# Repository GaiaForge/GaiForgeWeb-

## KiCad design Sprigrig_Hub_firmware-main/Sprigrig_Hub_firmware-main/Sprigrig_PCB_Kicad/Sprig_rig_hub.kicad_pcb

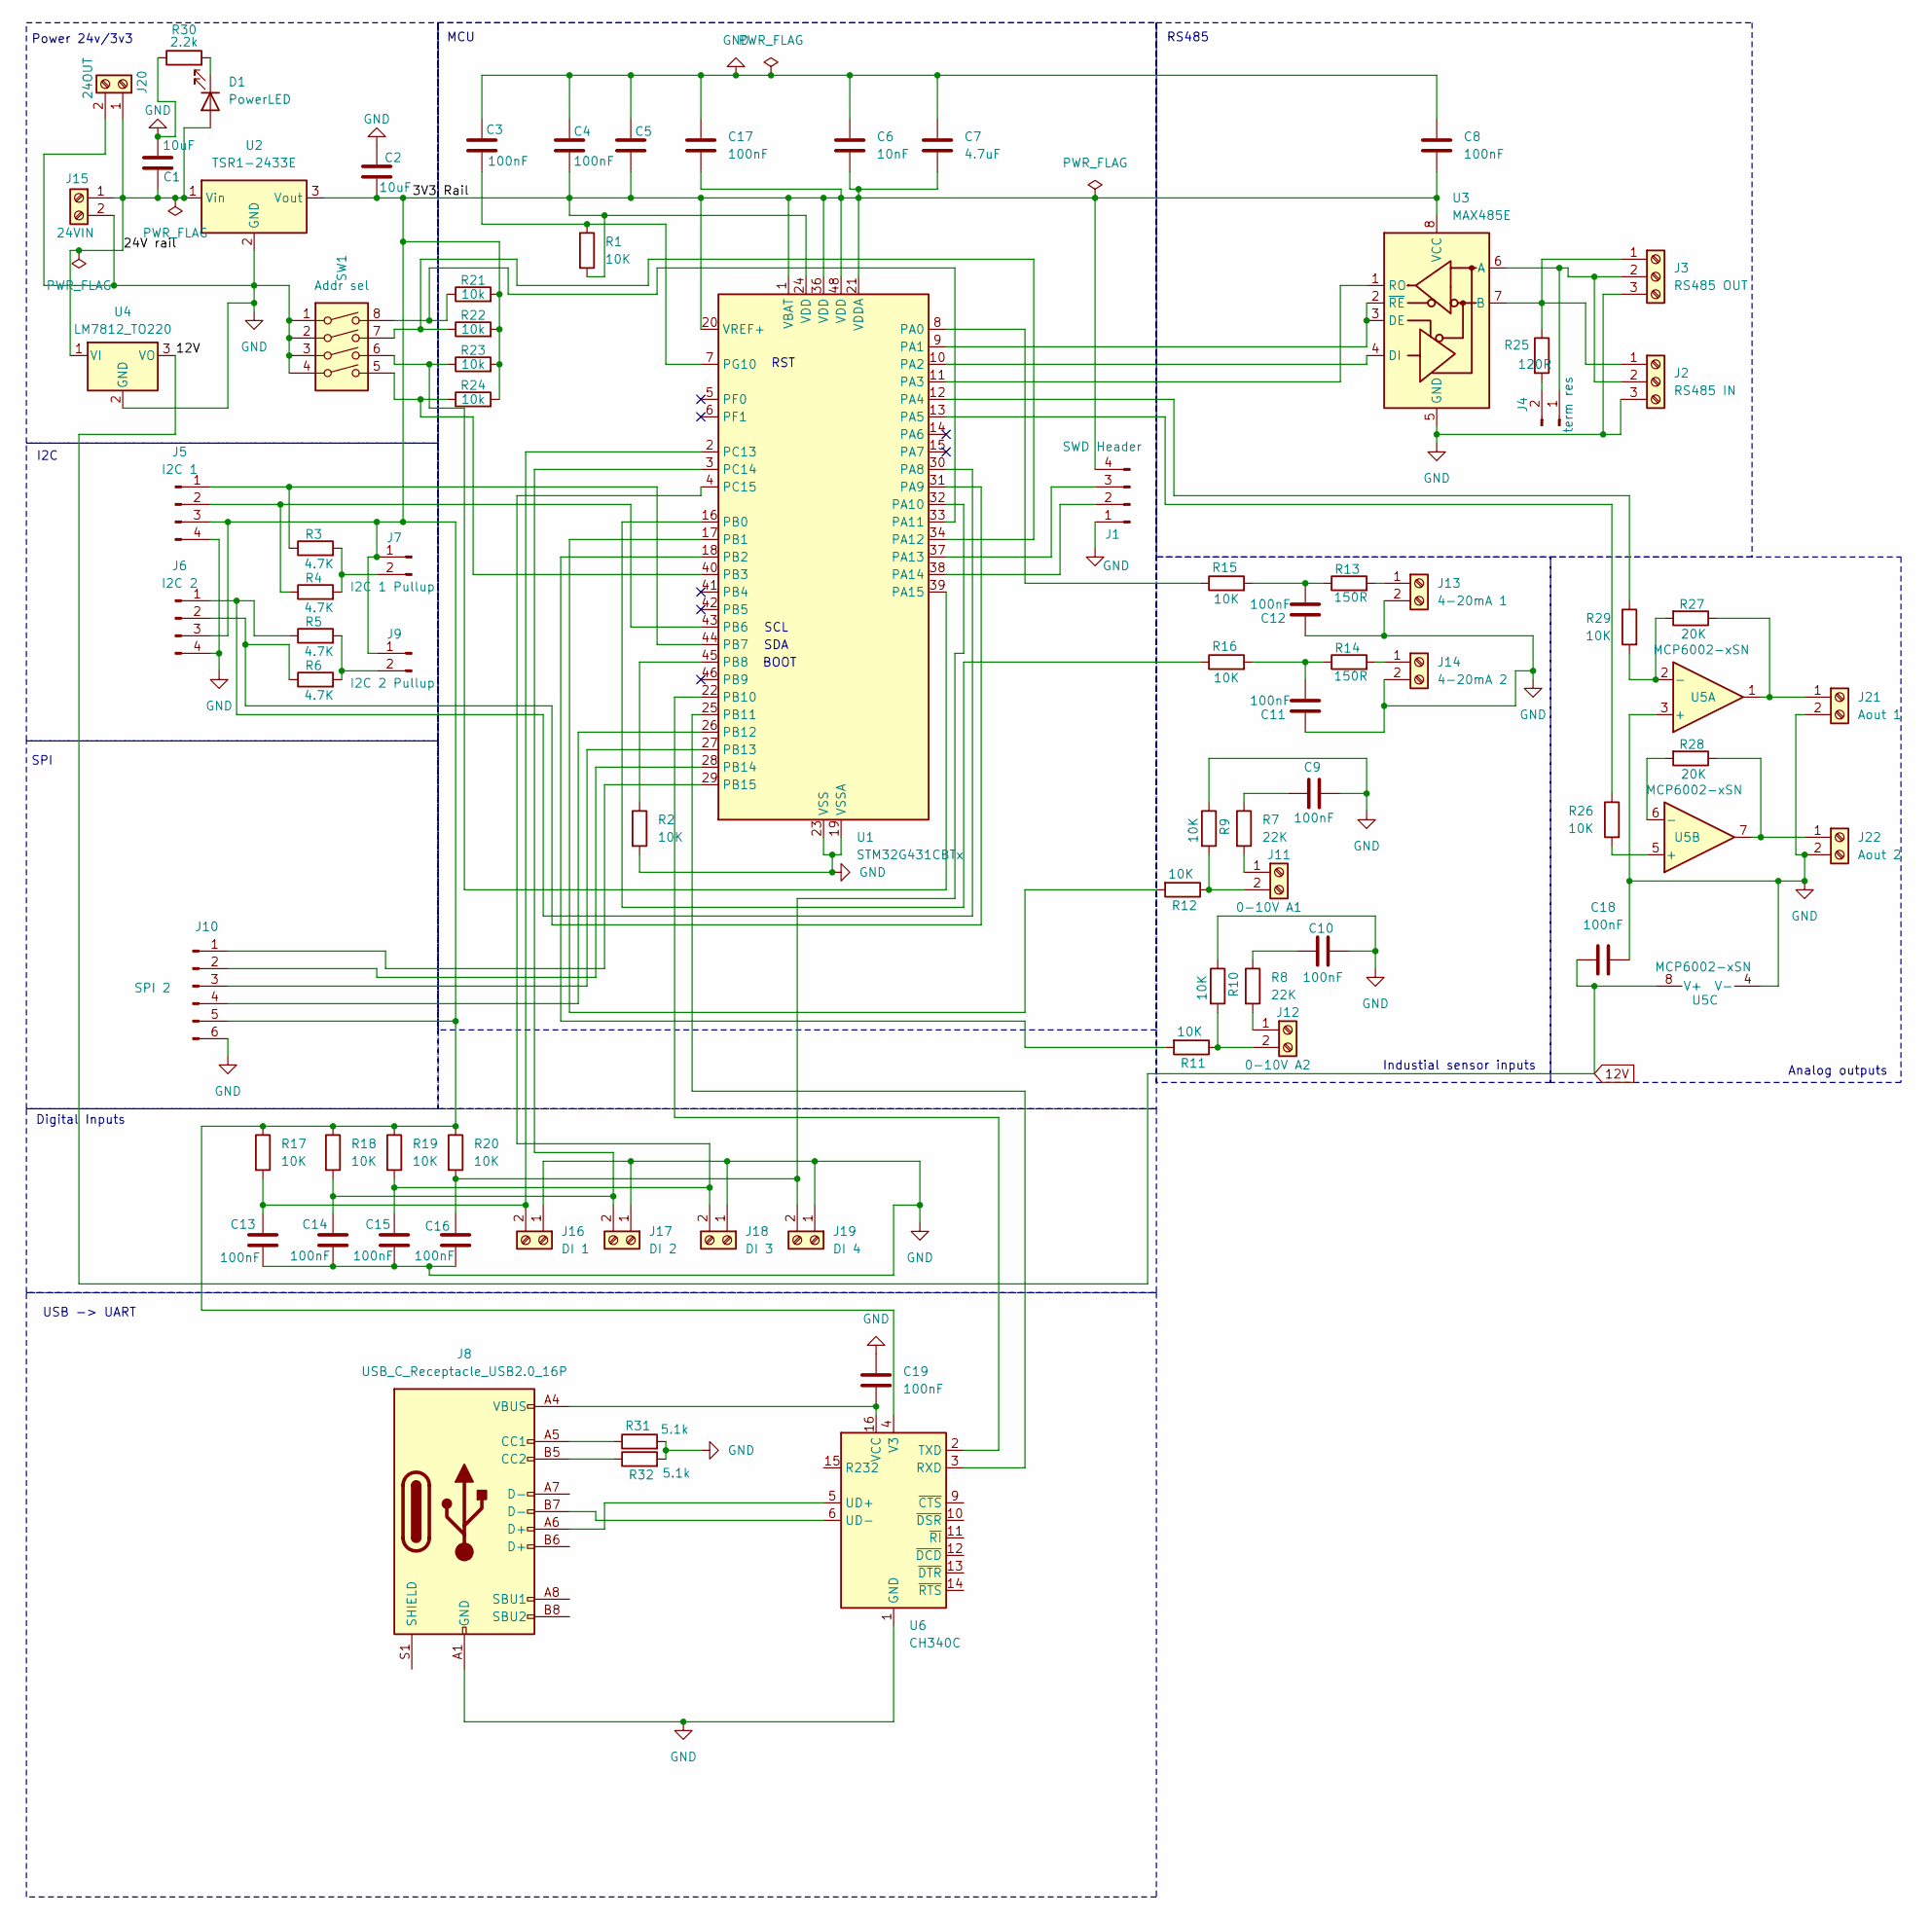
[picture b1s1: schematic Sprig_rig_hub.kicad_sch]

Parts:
C1, C2: 10uF; C_0805_2012Metric_Pad1.18x1.45mm_HandSolder; LCSC C15850
C3, C4, C5, C8, C9, C10, C11, C12, C13, C14, C15, C16, C17, C18: 100nF; C_0805_2012Metric_Pad1.18x1.45mm_HandSolder; LCSC C49678
C6: 10nF; C_0805_2012Metric_Pad1.18x1.45mm_HandSolder; LCSC C1710
C7: 4.7uF; C_0805_2012Metric_Pad1.18x1.45mm_HandSolder; LCSC C1779
C19: 100nF; C_0805_2012Metric_Pad1.18x1.45mm_HandSolder
D1: PowerLED; LED_0805_2012Metric_Pad1.15x1.40mm_HandSolder; LCSC C2297
J1: SWD Header; PinHeader_1x04_P2.54mm_Vertical; LCSC C2935932
J2: RS485 IN; TerminalBlock_MaiXu_MX126-5.0-03P_1x03_P5.00mm
J3: RS485 OUT; TerminalBlock_MaiXu_MX126-5.0-03P_1x03_P5.00mm
J4: term res; PinHeader_1x02_P2.54mm_Vertical; LCSC C2935934
J5: I2C 1; JST_XH_B4B-XH-A_1x04_P2.50mm_Vertical; LCSC C161870
J6: I2C 2; JST_XH_B4B-XH-A_1x04_P2.50mm_Vertical; LCSC C161870
J7: I2C 1 Pullup; PinHeader_1x02_P2.54mm_Vertical; LCSC C2935934
J8: USB_C_Receptacle_USB2.0_16P; USB_C_Receptacle_GCT_USB4105-xx-A_16P_TopMnt_Horizontal
J9: I2C 2 Pullup; PinHeader_1x02_P2.54mm_Vertical; LCSC C2935934
J10: SPI 2; JST_XH_B6B-XH-A_1x06_P2.50mm_Vertical; LCSC C161873
J11: 0-10V A1; TerminalBlock_MaiXu_MX126-5.0-02P_1x02_P5.00mm
J12: 0-10V A2; TerminalBlock_MaiXu_MX126-5.0-02P_1x02_P5.00mm
J13: 4-20mA 1; TerminalBlock_MaiXu_MX126-5.0-02P_1x02_P5.00mm
J14: 4-20mA 2; TerminalBlock_MaiXu_MX126-5.0-02P_1x02_P5.00mm
J15: 24VIN; TerminalBlock_MaiXu_MX126-5.0-02P_1x02_P5.00mm
J16: DI 1; TerminalBlock_MaiXu_MX126-5.0-02P_1x02_P5.00mm
J17: DI 2; TerminalBlock_MaiXu_MX126-5.0-02P_1x02_P5.00mm
J18: DI 3; TerminalBlock_MaiXu_MX126-5.0-02P_1x02_P5.00mm
J19: DI 4; TerminalBlock_MaiXu_MX126-5.0-02P_1x02_P5.00mm
J20: 24OUT; TerminalBlock_MaiXu_MX126-5.0-02P_1x02_P5.00mm
J21: Aout 1; TerminalBlock_MaiXu_MX126-5.0-02P_1x02_P5.00mm
J22: Aout 2; TerminalBlock_MaiXu_MX126-5.0-02P_1x02_P5.00mm
R1, R2, R9, R10, R11, R12, R15, R16, R17, R18, R19, R20, R26, R29: 10K; R_0805_2012Metric_Pad1.20x1.40mm_HandSolder; LCSC C17415
R3, R4, R5, R6: 4.7K; R_0805_2012Metric_Pad1.20x1.40mm_HandSolder; LCSC C17673
R7, R8: 22K; R_0805_2012Metric_Pad1.20x1.40mm_HandSolder; LCSC C17561
R13, R14: 150R; R_0805_2012Metric_Pad1.20x1.40mm_HandSolder; LCSC C17472
R21, R22, R23, R24: 10k; R_0805_2012Metric_Pad1.20x1.40mm_HandSolder; LCSC C17415
R25: 120R; R_0805_2012Metric_Pad1.20x1.40mm_HandSolder; LCSC C17446
R27, R28: 20K; R_0805_2012Metric_Pad1.20x1.40mm_HandSolder; LCSC C17560
R30: 2.2k; R_1206_3216Metric_Pad1.30x1.75mm_HandSolder; LCSC C4190
R31, R32: 5.1k; R_0805_2012Metric_Pad1.20x1.40mm_HandSolder
SW1: Addr sel; SW_DIP_SPSTx04_Slide_9.78x12.34mm_W7.62mm_P2.54mm; LCSC C15781
U1: STM32G431CBTx; LQFP-48_7x7mm_P0.5mm; LCSC C529355
U2: TSR1-2433E; Converter_DCDC_TRACO_TSR1-xxxxE_THT; LCSC C90637
U3: MAX485E; SOIC-8_3.9x4.9mm_P1.27mm; LCSC C19738
U4: LM7812_TO220; TO-263-3_TabPin2; LCSC C2877355
U5: MCP6002-xSN; SOIC-8_3.9x4.9mm_P1.27mm; LCSC C7377
U6: CH340C; SOIC-16_3.9x9.9mm_P1.27mm

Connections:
12V: C18.2, U4.3 (VO), U5.8 (V+)
/3V3 Rail: C2.1, C4.2, C5.2, C6.2, C7.2, C8.2, C17.2, J1.4 (VCC), J5.3 (VCC), J6.3 (VCC), J7.1, J9.1, J10.5 (3V3), R1.2, R17.1, R18.1, R19.1, R20.1, R21.2, R22.2, R23.2, R24.2, U1.1 (VBAT), U1.20 (VREF+), U1.21 (VDDA), U1.24 (VDD), U1.36 (VDD), U1.48 (VDD), U2.3 (Vout), U3.8 (VCC), U6.4 (V3)
/24V rail: C1.1, D1.2 (A), J15.1, J20.1, U2.1 (Vin), U4.1 (VI)
GND: C1.2, C2.2, C3.1, C4.1, C5.1, C6.1, C7.1, C8.1, C9.1, C10.1, C11.2, C12.2, C13.2, C14.2, C15.2, C16.2, C17.1, C18.1, C19.1, J1.1 (Gnd), J2.3, J3.3 (Gnd), J5.4 (Gnd), J6.4 (Gnd), J8.A1 (GND), J8.A12 (GND), J8.B1 (GND), J8.B12 (GND), J10.6 (Gnd), J13.2, J14.2, J15.2, J16.1, J17.1, J18.1, J19.1, J20.2, J21.2, J22.2, R2.2, R9.1, R10.1, R30.1, R31.2, R32.2, SW1.1, SW1.2, SW1.3, SW1.4, U1.19 (VSSA), U1.23 (VSS), U1.35 (VSS), U1.47 (VSS), U2.2 (GND), U3.5 (GND), U4.2 (GND), U5.3 (+), U5.4 (V-), U6.1 (GND)
unnamed: C9.2, R7.1
unnamed: C10.2, R8.1
unnamed: C11.1, R14.1, R16.2
unnamed: C12.1, R13.1, R15.2
unnamed: D1.1 (K), R30.2
unnamed: J1.2 (SWCLK), U1.38 (PA14)
unnamed: J1.3 (SWDIO), U1.37 (PA13)
unnamed: J2.1, J3.1 (B), R25.1, U3.7 (B)
unnamed: J2.2, J3.2 (A), J4.1, U3.6 (A)
unnamed: J4.2, R25.2
unnamed: J5.2 (SCL), R4.1, U1.43 (PB6)
unnamed: J5.1 (SDA), R3.1, U1.44 (PB7)
unnamed: J6.2 (SCL), R6.1, U1.31 (PA9)
unnamed: J6.1 (SDA), R5.1, U1.30 (PA8)
unnamed: J7.2, R3.2, R4.2
unnamed: J8.A5 (CC1), R31.1
unnamed: J8.B5 (CC2), R32.1
unnamed: J9.2, R5.2, R6.2
unnamed: J10.4 (CS), U1.26 (PB12)
unnamed: J10.2 (MISO), U1.28 (PB14)
unnamed: J10.1 (MOSI), U1.29 (PB15)
unnamed: J10.3 (SCK), U1.27 (PB13)
unnamed: J11.2 (Gnd), R9.2, R12.1
unnamed: J11.1, R7.2
unnamed: J12.2 (Gnd), R10.2, R11.1
unnamed: J12.1, R8.2
unnamed: J13.1, R13.2
unnamed: J14.1, R14.2
unnamed: C13.1, J16.2, R17.2, U1.2 (PC13)
unnamed: C14.1, J17.2, R18.2, U1.3 (PC14)
unnamed: C15.1, J18.2, R19.2, U1.4 (PC15)
unnamed: C16.1, J19.2, R20.2, U1.32 (PA10)
unnamed: J21.1, R27.1, U5.1
unnamed: J22.1, R28.1, U5.7
unnamed: R15.1, U1.8 (PA0)
unnamed: U1.9 (PA1), U3.2 (~RE), U3.3 (DE)
unnamed: U1.10 (PA2), U3.4 (DI)
unnamed: U1.11 (PA3), U3.1 (RO)
unnamed: R29.1, U1.12 (PA4)
unnamed: R26.1, U1.13 (PA5)
unnamed: R21.1, SW1.8, U1.33 (PA11)
unnamed: R22.1, SW1.7, U1.34 (PA12)
unnamed: R23.1, SW1.6, U1.39 (PA15)
unnamed: R16.1, U1.16 (PB0)
unnamed: R12.2, U1.17 (PB1)
unnamed: R11.2, U1.18 (PB2)
unnamed: R24.1, SW1.5, U1.40 (PB3)
unnamed: R2.1, U1.45 (PB8)
unnamed: U1.22 (PB10), U6.2 (TXD)
unnamed: U1.25 (PB11), U6.3 (RXD)
unnamed: C3.2, R1.1, U1.7 (PG10)
unnamed: R27.2, R29.2, U5.2 (-)
unnamed: R26.2, U5.5 (+)
unnamed: R28.2, U5.6 (-)
unnamed: J8.A6 (D+), U6.5 (UD+)
unnamed: J8.B7 (D-), U6.6 (UD-)
unnamed: C19.2, J8.A4 (VBUS), J8.A9 (VBUS), J8.B4 (VBUS), J8.B9 (VBUS), U6.16 (VCC)

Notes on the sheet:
SPI
USB -> UART
MCU
SDA
I2C
Industial sensor inputs
Power 24v/3v3
RS485
Digital Inputs
BOOT
SCL
RST
Analog outputs

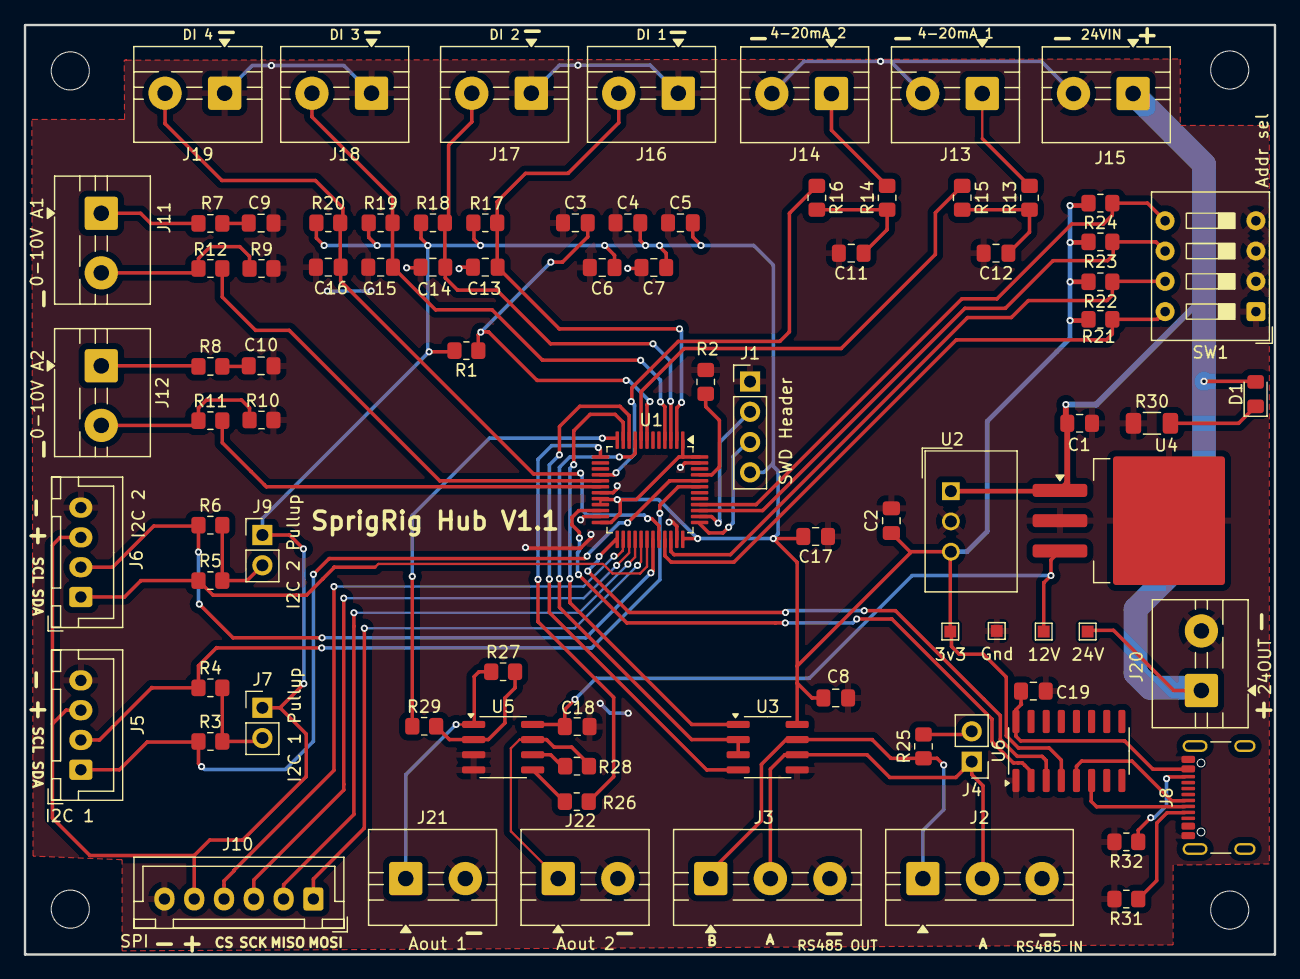
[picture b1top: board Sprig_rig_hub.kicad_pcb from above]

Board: 2 copper layers, 104.9 x 78.0 mm, 81 parts (0 on the bottom side), 61 nets.

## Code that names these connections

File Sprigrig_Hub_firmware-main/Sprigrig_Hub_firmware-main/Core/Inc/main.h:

/**
 * SprigRig Sensor Hub Firmware
 * STM32G431CBT6
 */

#ifndef __MAIN_H
#define __MAIN_H

#ifdef __cplusplus
extern "C" {
#endif

#include "stm32g4xx_hal.h"

/* Exported defines */

// RS485 DE/RE Control - PA1 per netlist
#define RS485_DE_PORT       GPIOA
#define RS485_DE_PIN        GPIO_PIN_1

// DIP Switches (Address Selection) - Active low with pullups
#define DIP_SW1_PORT        GPIOA
#define DIP_SW1_PIN         GPIO_PIN_11  // SW1 pin 8 -> PA11
#define DIP_SW2_PORT        GPIOA
#define DIP_SW2_PIN         GPIO_PIN_12  // SW1 pin 7 -> PA12
#define DIP_SW3_PORT        GPIOA
#define DIP_SW3_PIN         GPIO_PIN_15  // SW1 pin 6 -> PA15
#define DIP_SW4_PORT        GPIOB
#define DIP_SW4_PIN         GPIO_PIN_3   // SW1 pin 5 -> PB3

// Digital Inputs - Active low with pullups
#define DI1_PORT            GPIOC
#define DI1_PIN             GPIO_PIN_13  // J16 -> PC13
#define DI2_PORT            GPIOC
#define DI2_PIN             GPIO_PIN_14  // J17 -> PC14
#define DI3_PORT            GPIOC
#define DI3_PIN             GPIO_PIN_15  // J18 -> PC15
#define DI4_PORT            GPIOA
#define DI4_PIN             GPIO_PIN_10  // J19 -> PA10

// I2C1 (Sensor Bus 1) - PB6/PB7
#define I2C1_SCL_PORT       GPIOB
#define I2C1_SCL_PIN        GPIO_PIN_6
#define I2C1_SDA_PORT       GPIOB
#define I2C1_SDA_PIN        GPIO_PIN_7

// I2C2 (Sensor Bus 2) - PA8/PA9
#define I2C2_SDA_PORT       GPIOA
#define I2C2_SDA_PIN        GPIO_PIN_8
#define I2C2_SCL_PORT       GPIOA
#define I2C2_SCL_PIN        GPIO_PIN_9

// SPI2 (Expansion) - PB12-15
#define SPI2_CS_PORT        GPIOB
#define SPI2_CS_PIN         GPIO_PIN_12
#define SPI2_SCK_PIN        GPIO_PIN_13
#define SPI2_MISO_PIN       GPIO_PIN_14
#define SPI2_MOSI_PIN       GPIO_PIN_15

// ADC Channels - Per STM32G431 datasheet
#define ADC_4_20MA_1_CH     ADC_CHANNEL_1   // PA0 - ADC1_IN1 (J13 via R13)
#define ADC_4_20MA_2_CH     ADC_CHANNEL_15  // PB0 - ADC1_IN15 (J14)
#define ADC_0_10V_1_CH      ADC_CHANNEL_12  // PB1 - ADC1_IN12 (via R12 voltage divider)
#define ADC_0_10V_2_CH      ADC_CHANNEL_11  // PB2 - ADC2_IN12, but ADC1_IN11 on shared ADC1

// DAC Outputs (0-10V)
#define DAC_OUT1_PIN        GPIO_PIN_4      // PA4 - DAC1_OUT1
#define DAC_OUT1_PORT       GPIOA
#define DAC_OUT2_PIN        GPIO_PIN_5      // PA5 - DAC1_OUT2
#define DAC_OUT2_PORT       GPIOA

// Modbus Register Map
#define REG_CHANNEL_1       0   // First sensor channel
#define REG_CHANNEL_2       1
#define REG_CHANNEL_3       2
#define REG_CHANNEL_4       3
#define REG_CHANNEL_5       4
#define REG_CHANNEL_6       5
#define REG_CHANNEL_7       6
#define REG_CHANNEL_8       7
#define REG_DI_STATUS       8   // Digital inputs as bits
#define REG_HUB_ID          9   // Hub identifier
#define REG_FW_VERSION      10  // Firmware version
#define REG_AOUT_1          11  // Analog output 1 (0-10V) - writable
#define REG_AOUT_2          12  // Analog output 2 (0-10V) - writable

#define HOLDING_REG_COUNT   16

/* Exported functions */
void Error_Handler(void);

#ifdef __cplusplus
}
#endif

#endif /* __MAIN_H */

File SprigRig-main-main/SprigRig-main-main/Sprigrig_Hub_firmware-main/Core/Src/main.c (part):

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    __HAL_RCC_ADC12_CLK_ENABLE();

    /* Configure ADC GPIO pins */
    // PA0 - ADC1_IN1 (4-20mA #1)
    // PB0 - ADC1_IN15 (4-20mA #2)
    // PB1 - ADC1_IN12 (0-10V #1)
    // PB2 - ADC1_IN11 (0-10V #2)

    GPIO_InitStruct.Mode = GPIO_MODE_ANALOG;
    GPIO_InitStruct.Pull = GPIO_NOPULL;
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}

/**
 * I2C1 Initialization (PB6=SCL, PB7=SDA)
 */
static void MX_I2C1_Init(void) {
    GPIO_InitTypeDef GPIO_InitStruct = {0};
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}

/**
 * I2C2 Initialization (PA8=SDA, PA9=SCL)
 */
static void MX_I2C2_Init(void) {
    GPIO_InitTypeDef GPIO_InitStruct = {0};
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}

/**
 * DAC1 Initialization (PA4=OUT1, PA5=OUT2)
 * Used for 0-10V analog outputs
 */
static void MX_DAC1_Init(void) {
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        Error_Handler();
    }

    /* Configure DAC channel 1 (PA4) */
    sConfig.DAC_HighFrequency = DAC_HIGH_FREQUENCY_INTERFACE_MODE_AUTOMATIC;
    sConfig.DAC_DMADoubleDataMode = DISABLE;
    sConfig.DAC_SignedFormat = DISABLE;
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        Error_Handler();
    }

    /* Configure DAC channel 2 (PA5) */
    if (HAL_DAC_ConfigChannel(&hdac1, &sConfig, DAC_CHANNEL_2) != HAL_OK) {
        Error_Handler();
    }
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    __HAL_RCC_SPI2_CLK_ENABLE();

    /* Configure SPI2 GPIO pins */
    // PB13 = SCK, PB14 = MISO, PB15 = MOSI, PB12 = CS (manual)
    GPIO_InitStruct.Pin = GPIO_PIN_13 | GPIO_PIN_14 | GPIO_PIN_15;
    GPIO_InitStruct.Mode = GPIO_MODE_AF_PP;
    GPIO_InitStruct.Pull = GPIO_NOPULL;
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
/**
 * USART2 Initialization (RS485 for Modbus)
 * PA2 = TX, PA3 = RX
 */
static void MX_USART2_UART_Init(void) {
    GPIO_InitTypeDef GPIO_InitStruct = {0};
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
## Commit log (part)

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2025-12-29 Test deployment workflow
2025-12-29 Test deployment with new SSH key
2025-12-29 Test webhook deployment
2025-12-29 Fix: Use HTTPS for git clone in deploy script
2025-12-29 Test auto-deployment via webhook
2025-12-29 Test webhook auto-deployment
2025-12-29 Final webhook test
2025-12-30 Fix mobile menu and header clipping issues
2025-12-30 Remove GitHub Actions workflow - using webhook instead
2025-12-30 Remove GitHub Actions workflow and fix mobile padding
2025-12-30 Rename User Guide to User Manual
2025-12-30 Fix table header gradient - use correct CSS variable
2025-12-30 Center product hero images and text
2025-12-30 Increase product hero image size to 350px
2025-12-30 Increase product hero image size on mobile devices
2026-02-28 Contact form: submit via fetch to /send-contact mailer
2026-02-28 Fix: Schlammwiss nature preserve → nature reserve
2026-03-15 Add HiveGuard product page, update nav dropdowns and footer links
2026-03-20 Add recovered portal source files
